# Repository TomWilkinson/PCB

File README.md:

This is a collection of some of my PCB designs

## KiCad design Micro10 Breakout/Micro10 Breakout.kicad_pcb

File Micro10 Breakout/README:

This was used to moust a NLAS4684MR2G to a breadboard.  It might be useful for other devices that use Micro-10
You can also oerder it from OSH Park https://oshpark.com/shared_projects/GnWUjyM9

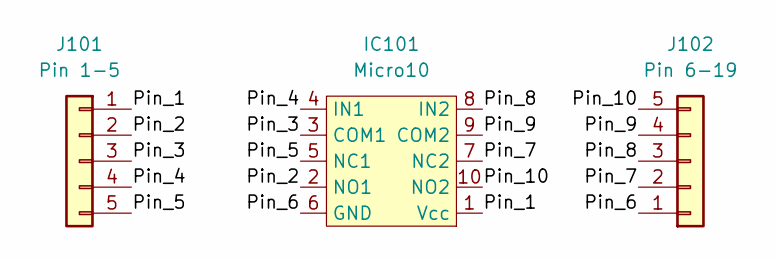
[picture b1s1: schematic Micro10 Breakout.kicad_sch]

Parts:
IC101: Micro10; MICRO10_3X3_ONS; Manufacturer_Part_Number NLAS4684MR2G; DIgi-Key Part Number NLAS4684MR2GOSCT-ND
J101: Pin 1-5; PinHeader_1x05_P2.54mm_Vertical
J102: Pin 6-19; PinHeader_1x05_P2.54mm_Vertical

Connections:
/Pin_1: IC101.1 (Vcc), J101.1
/Pin_2: IC101.2 (NO1), J101.2
/Pin_3: IC101.3 (COM1), J101.3
/Pin_4: IC101.4 (IN1), J101.4
/Pin_5: IC101.5 (NC1), J101.5
/Pin_6: IC101.6 (GND), J102.1
/Pin_7: IC101.7 (NC2), J102.2
/Pin_8: IC101.8 (IN2), J102.3
/Pin_9: IC101.9 (COM2), J102.4
/Pin_10: IC101.10 (NO2), J102.5

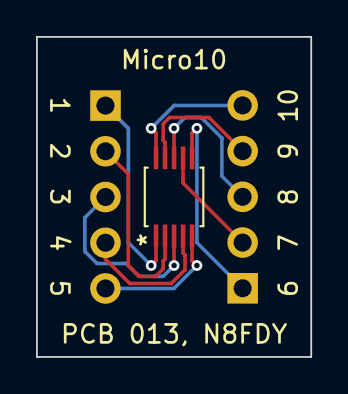
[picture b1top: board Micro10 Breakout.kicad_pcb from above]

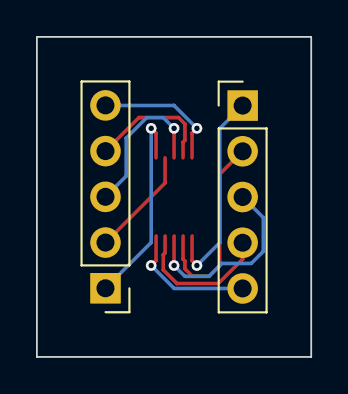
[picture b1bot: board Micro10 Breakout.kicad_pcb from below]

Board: 2 copper layers, 15.2 x 17.8 mm, 3 parts (2 on the bottom side), 10 nets.

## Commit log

2024-02-20 Version 1
2024-02-20 Update README.md
    Added link to OSH Park
2024-02-20 Update README.md
    Removed line meant for a different readme
2024-02-20 Update Readme
    Added OSH Park link
